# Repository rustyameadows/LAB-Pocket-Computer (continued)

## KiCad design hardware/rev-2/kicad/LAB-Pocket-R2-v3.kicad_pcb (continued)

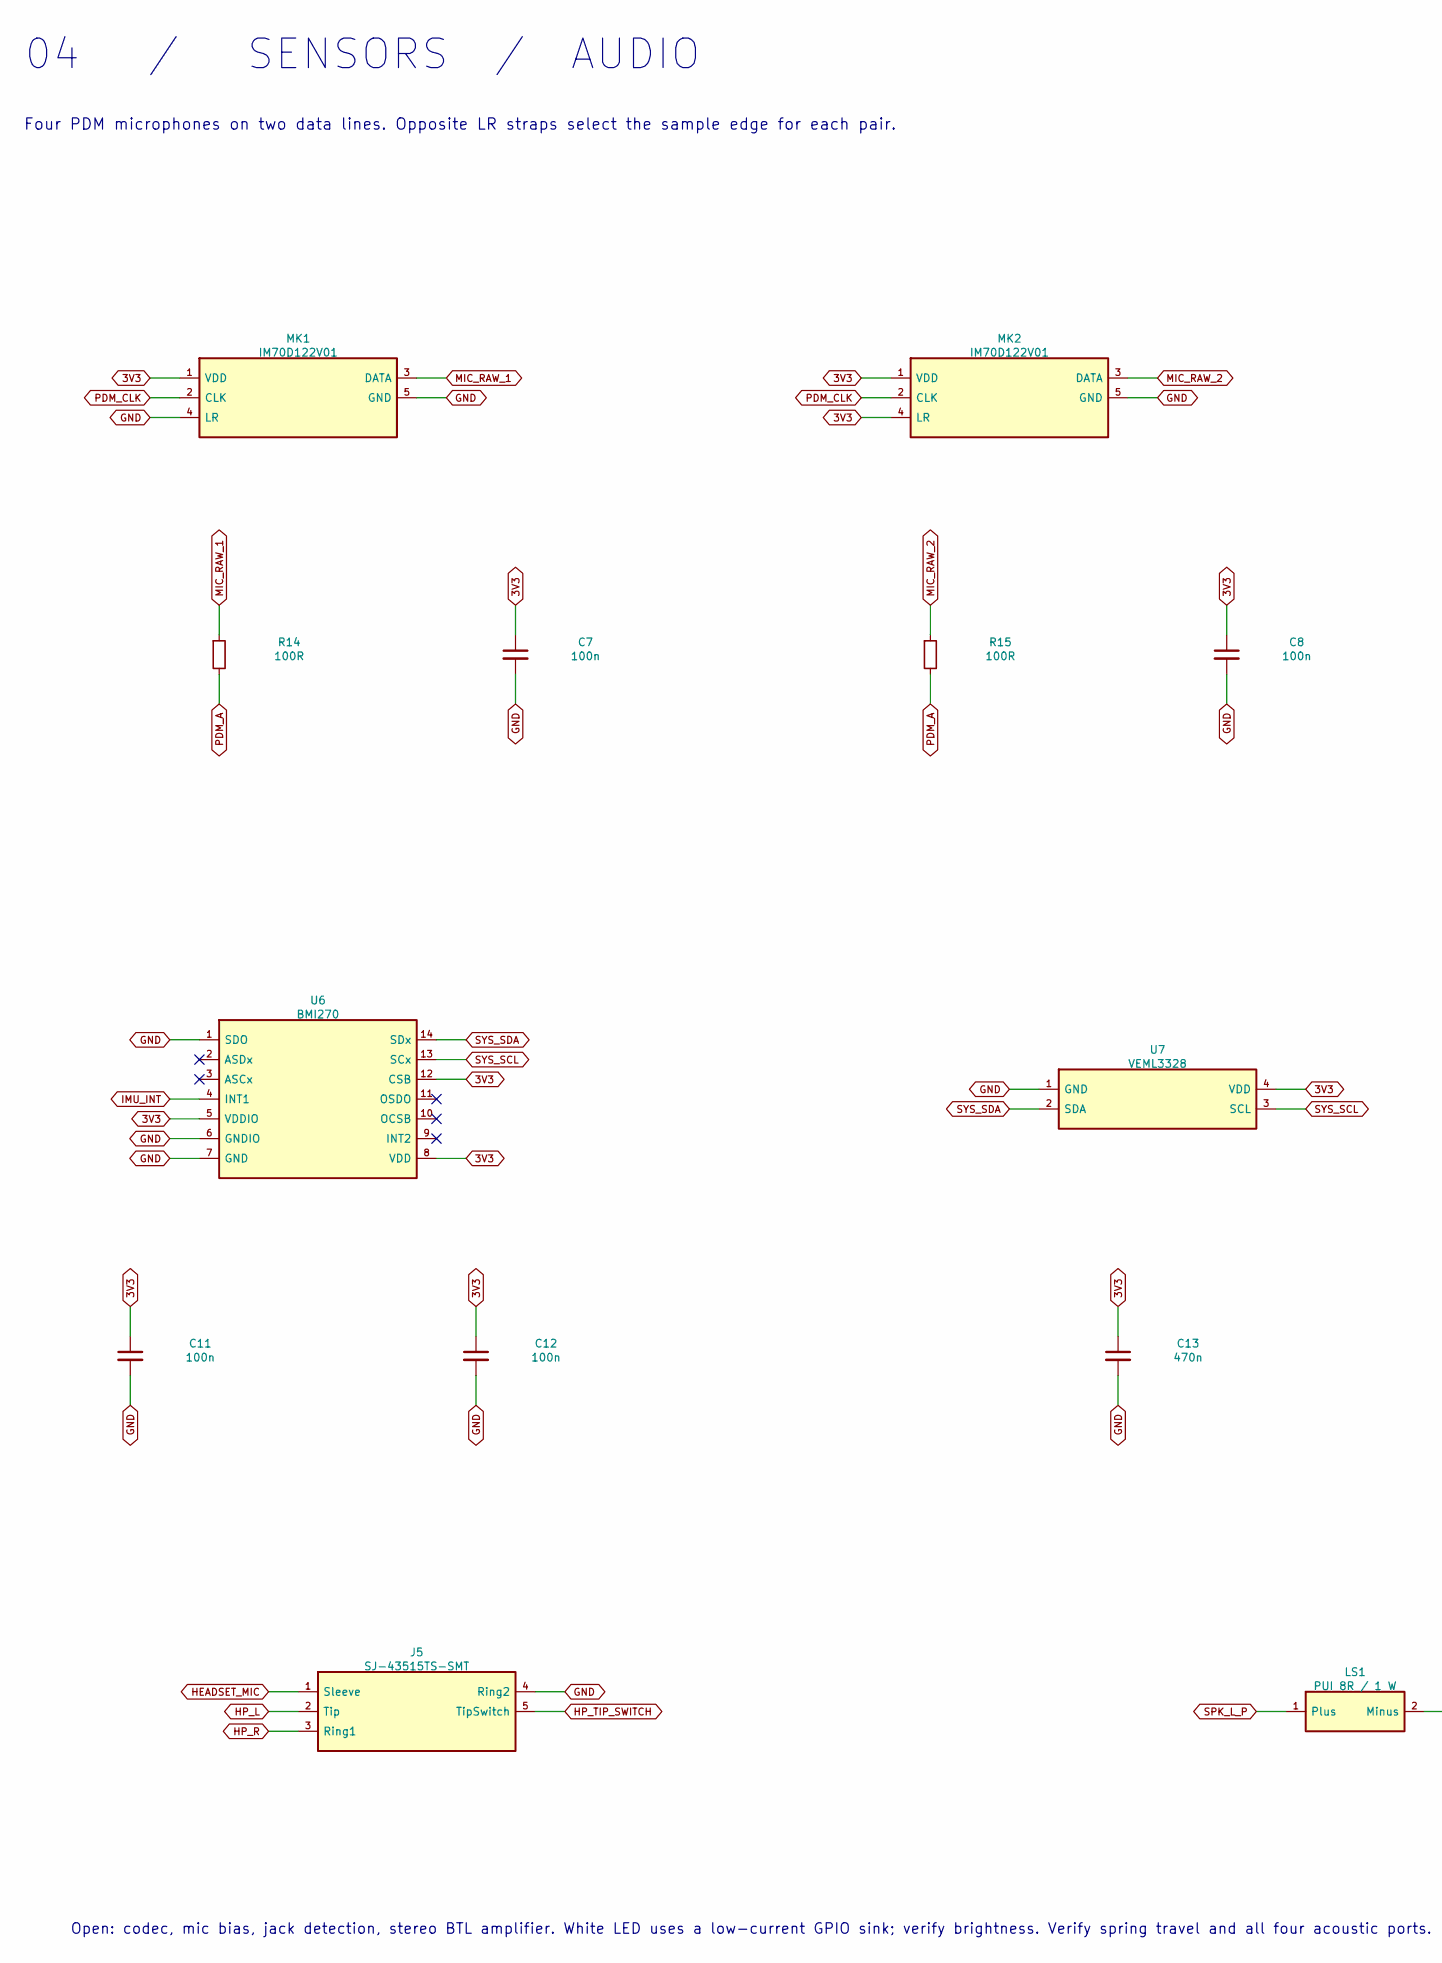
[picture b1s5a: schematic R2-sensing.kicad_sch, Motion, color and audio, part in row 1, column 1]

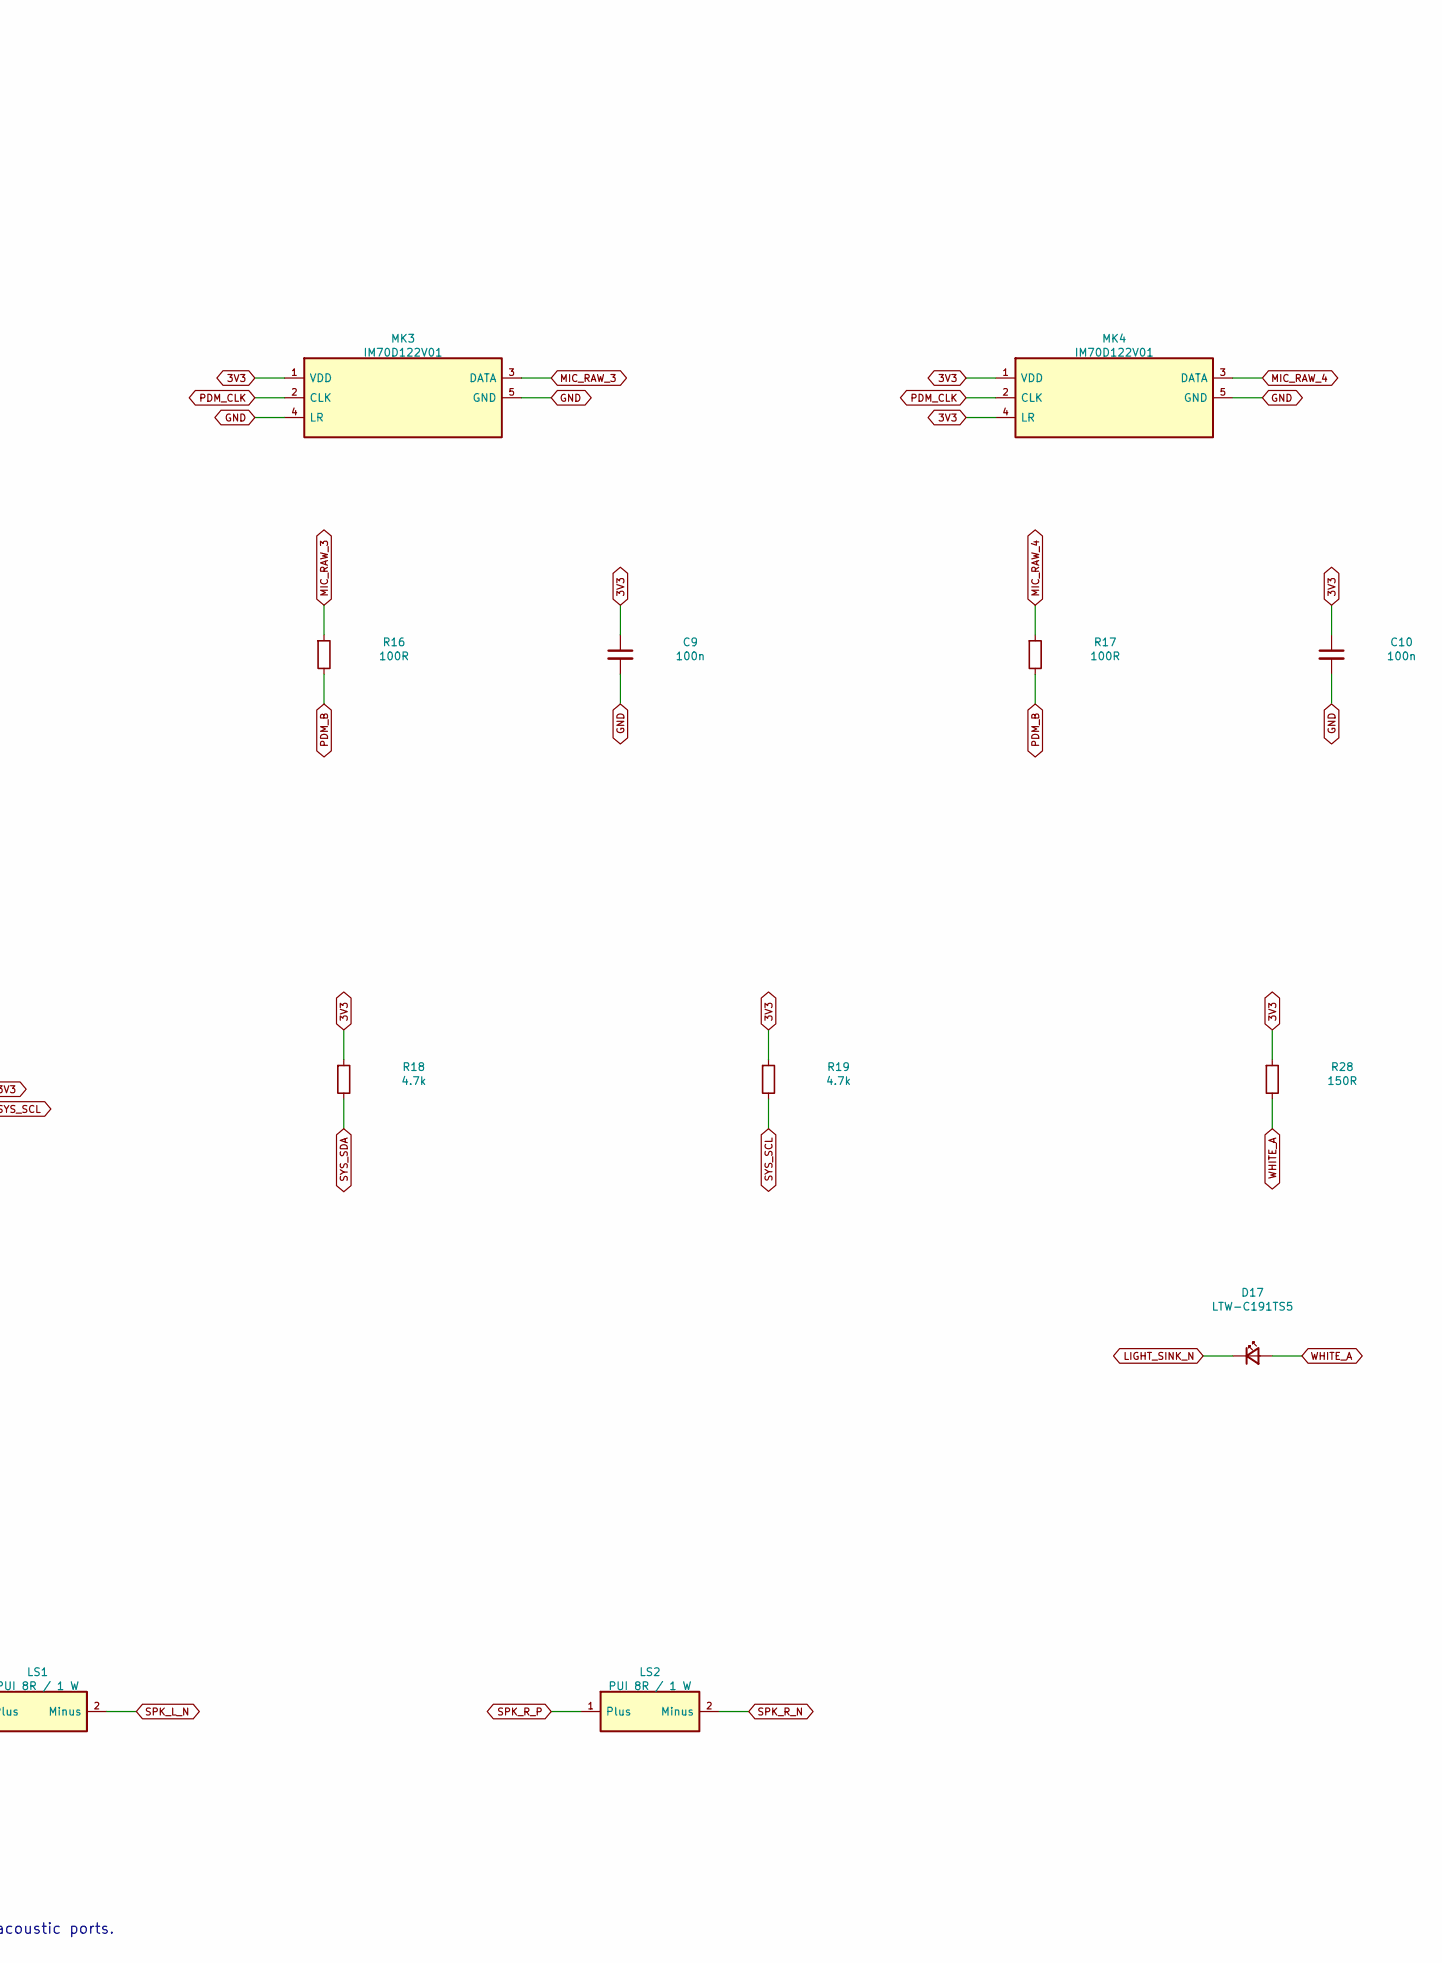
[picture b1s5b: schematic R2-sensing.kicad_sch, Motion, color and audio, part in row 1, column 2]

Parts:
C7, C8, C9, C10, C11, C12: 100n; C_0603_1608Metric; MPN C0603C104K5RACTU
C13: 470n; C_0603_1608Metric; MPN C0603C474K3RACTU
D17: LTW-C191TS5; LED_0603_1608Metric; MPN LTW-C191TS5
J5: SJ-43515TS-SMT; SJ-43515TS; MPN SJ-43515TS-SMT-TR
LS1, LS2: PUI 8R / 1 W; MPN AS01808AO-SC18-WP-R
MK1, MK2, MK3, MK4: IM70D122V01; IM70D122; MPN IM70D122V01XTMA1
R14, R15, R16, R17: 100R; R_0603_1608Metric; MPN CRCW0603100RFKEA
R18, R19: 4.7k; R_0603_1608Metric; MPN CRCW06034K70FKEA
R28: 150R; R_0603_1608Metric; MPN CRCW0603150RFKEA
U6: BMI270; Bosch_LGA-14_3x2.5mm_P0.5mm; MPN BMI270
U7: VEML3328; MPN VEML3328

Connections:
3V3: C7.1, C8.1, C9.1, C10.1, C11.1, C12.1, C13.1, MK1.1 (VDD), MK2.1 (VDD), MK2.4 (LR), MK3.1 (VDD), MK4.1 (VDD), MK4.4 (LR), R18.1, R19.1, R28.1, U6.5 (VDDIO), U6.8 (VDD), U6.12 (CSB), U7.4 (VDD); also elsewhere on the board
GND: C7.2, C8.2, C9.2, C10.2, C11.2, C12.2, C13.2, J5.4 (Ring2), MK1.4 (LR), MK1.5 (GND), MK2.5 (GND), MK3.4 (LR), MK3.5 (GND), MK4.5 (GND), U6.1 (SDO), U6.6 (GNDIO), U6.7 (GND), U7.1 (GND); also elsewhere on the board
HEADSET_MIC: J5.1 (Sleeve)
HP_L: J5.2 (Tip)
HP_R: J5.3 (Ring1)
HP_TIP_SWITCH: J5.5 (TipSwitch)
IMU_INT: U6.4 (INT1); also elsewhere on the board
LIGHT_SINK_N: D17.1 (K); also elsewhere on the board
MIC_RAW_1: MK1.3 (DATA), R14.1
MIC_RAW_2: MK2.3 (DATA), R15.1
MIC_RAW_3: MK3.3 (DATA), R16.1
MIC_RAW_4: MK4.3 (DATA), R17.1
PDM_A: R14.2, R15.2; also elsewhere on the board
PDM_B: R16.2, R17.2; also elsewhere on the board
PDM_CLK: MK1.2 (CLK), MK2.2 (CLK), MK3.2 (CLK), MK4.2 (CLK); also elsewhere on the board
SYS_SCL: R19.2, U6.13 (SCx), U7.3 (SCL); also elsewhere on the board
SYS_SDA: R18.2, U6.14 (SDx), U7.2 (SDA); also elsewhere on the board
WHITE_A: D17.2 (A), R28.2

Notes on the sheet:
04 / SENSORS / AUDIO
Four PDM microphones on two data lines. Opposite LR straps select the sample edge for each pair.
Open: codec, mic bias, jack detection, stereo BTL amplifier. White LED uses a low-current GPIO sink; verify brightness. Verify spring travel and all four acoustic ports.

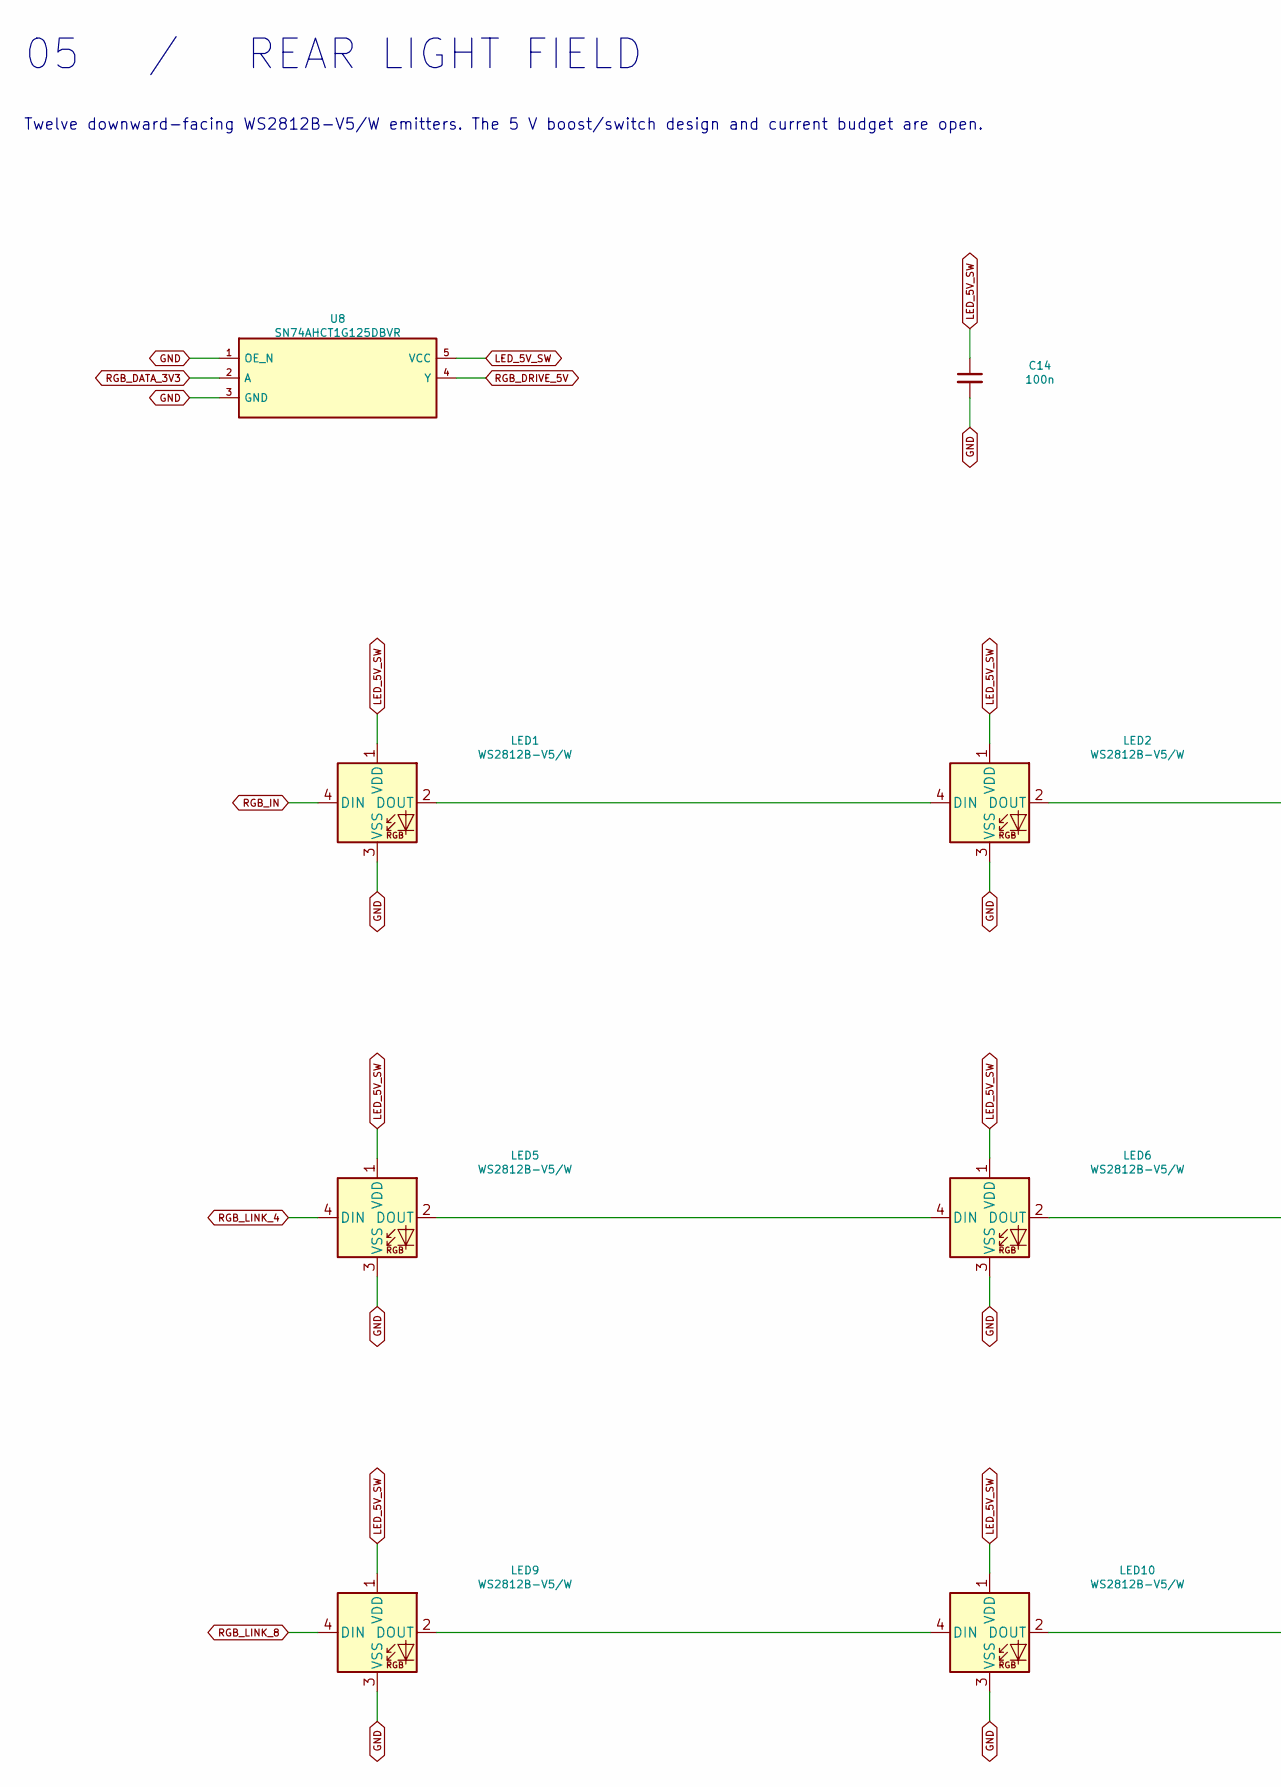
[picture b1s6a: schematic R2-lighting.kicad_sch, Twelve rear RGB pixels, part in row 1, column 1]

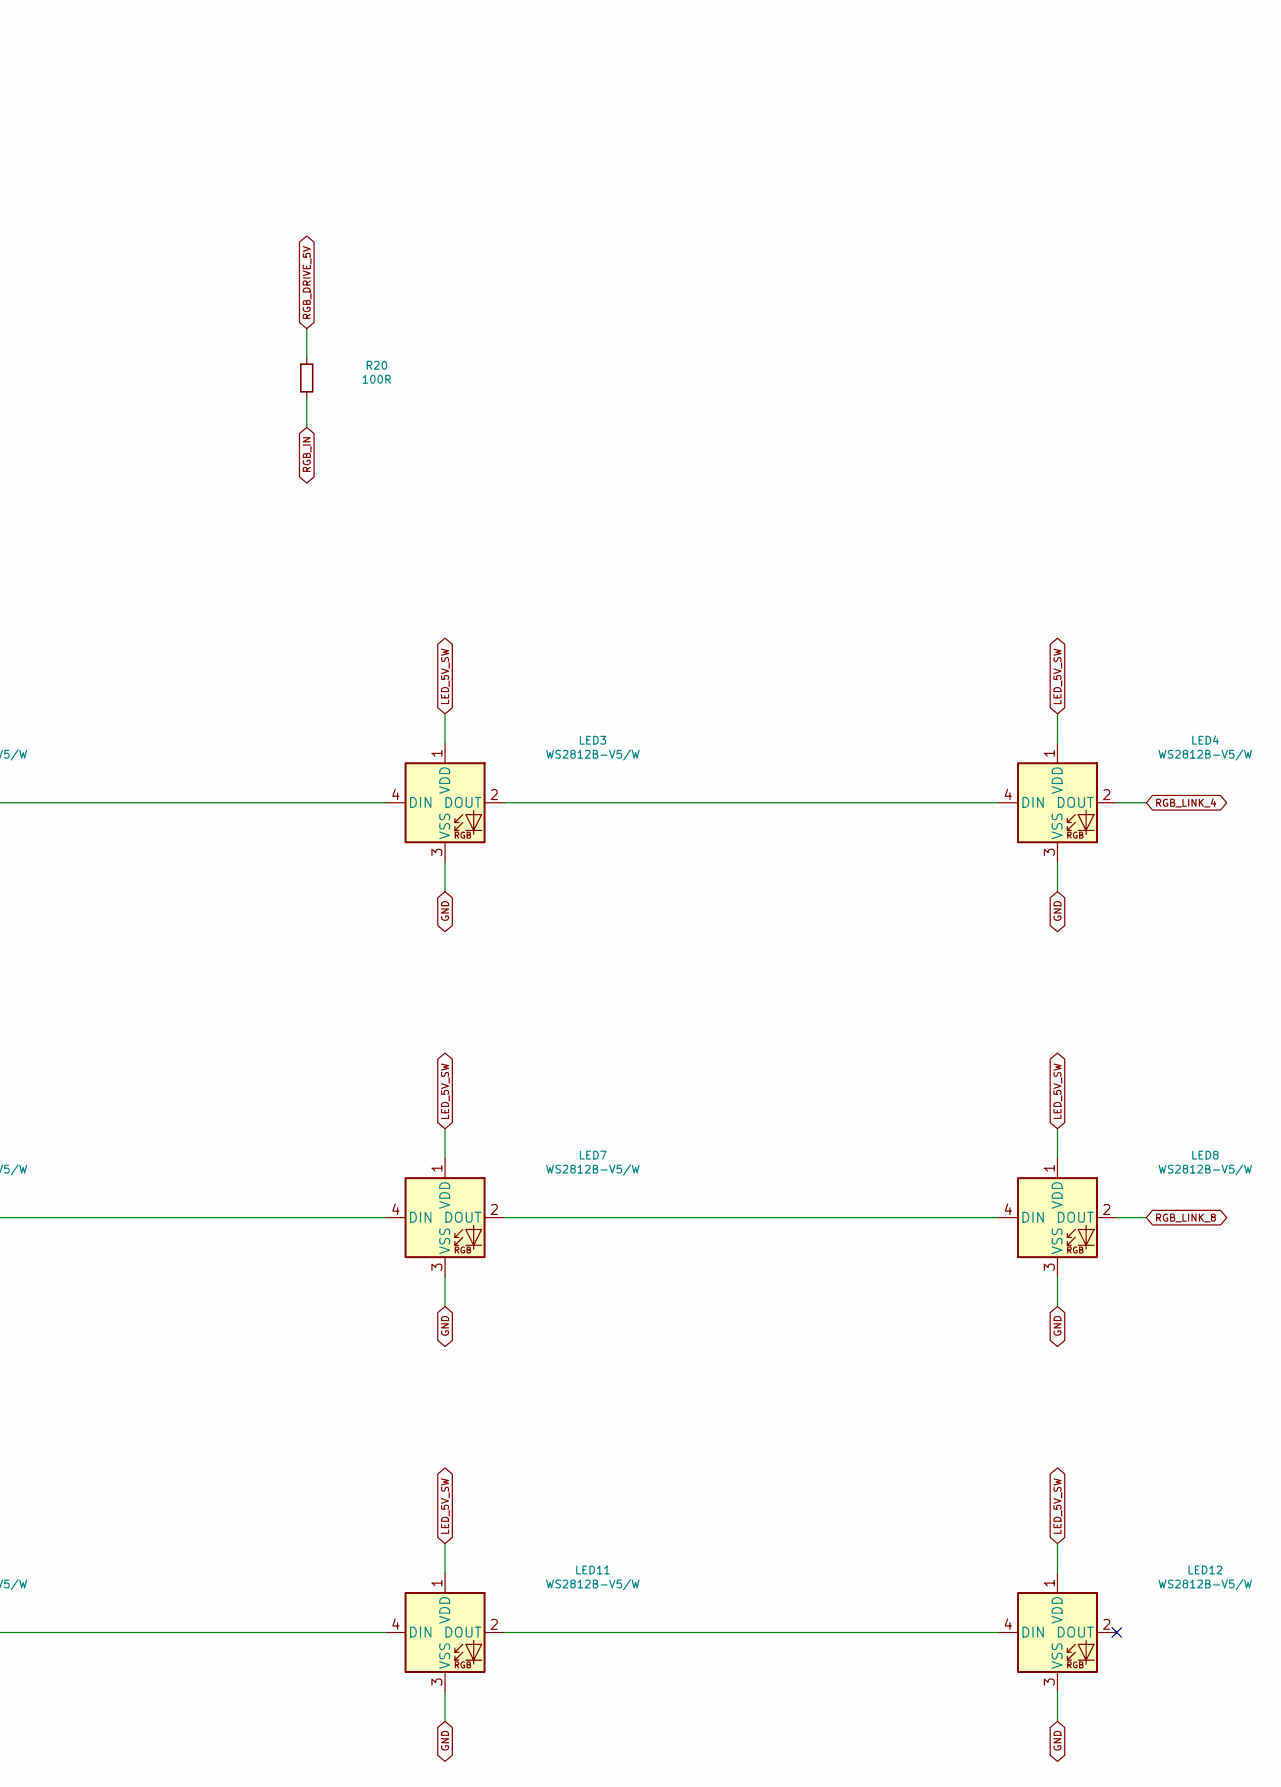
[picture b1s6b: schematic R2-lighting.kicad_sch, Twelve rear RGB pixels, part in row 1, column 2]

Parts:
C14: 100n; C_0603_1608Metric; MPN C0603C104K5RACTU
LED1, LED2, LED3, LED4, LED5, LED6, LED7, LED8, LED9, LED10, LED11, LED12: WS2812B-V5/W; LED_WS2812B_PLCC4_5.0x5.0mm_P3.2mm; MPN WS2812B-V5/W
R20: 100R; R_0603_1608Metric; MPN CRCW0603100RFKEA
U8: SN74AHCT1G125DBVR; SOT-23-5; MPN SN74AHCT1G125DBVR

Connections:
GND: C14.2, LED1.3 (VSS), LED2.3 (VSS), LED3.3 (VSS), LED4.3 (VSS), LED5.3 (VSS), LED6.3 (VSS), LED7.3 (VSS), LED8.3 (VSS), LED9.3 (VSS), LED10.3 (VSS), LED11.3 (VSS), LED12.3 (VSS), U8.1 (OE_N), U8.3 (GND); also elsewhere on the board
LED_5V_SW: C14.1, LED1.1 (VDD), LED2.1 (VDD), LED3.1 (VDD), LED4.1 (VDD), LED5.1 (VDD), LED6.1 (VDD), LED7.1 (VDD), LED8.1 (VDD), LED9.1 (VDD), LED10.1 (VDD), LED11.1 (VDD), LED12.1 (VDD), U8.5 (VCC)
unnamed: LED1.2 (DOUT), LED2.4 (DIN)
unnamed: LED2.2 (DOUT), LED3.4 (DIN)
unnamed: LED3.2 (DOUT), LED4.4 (DIN)
unnamed: LED5.2 (DOUT), LED6.4 (DIN)
unnamed: LED6.2 (DOUT), LED7.4 (DIN)
unnamed: LED7.2 (DOUT), LED8.4 (DIN)
unnamed: LED9.2 (DOUT), LED10.4 (DIN)
unnamed: LED10.2 (DOUT), LED11.4 (DIN)
unnamed: LED11.2 (DOUT), LED12.4 (DIN)
RGB_DATA_3V3: U8.2 (A); also elsewhere on the board
RGB_DRIVE_5V: R20.1, U8.4 (Y)
RGB_IN: LED1.4 (DIN), R20.2
RGB_LINK_4: LED4.2 (DOUT), LED5.4 (DIN)
RGB_LINK_8: LED8.2 (DOUT), LED9.4 (DIN)

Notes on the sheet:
05 / REAR LIGHT FIELD
Twelve downward-facing WS2812B-V5/W emitters. The 5 V boost/switch design and current budget are open.

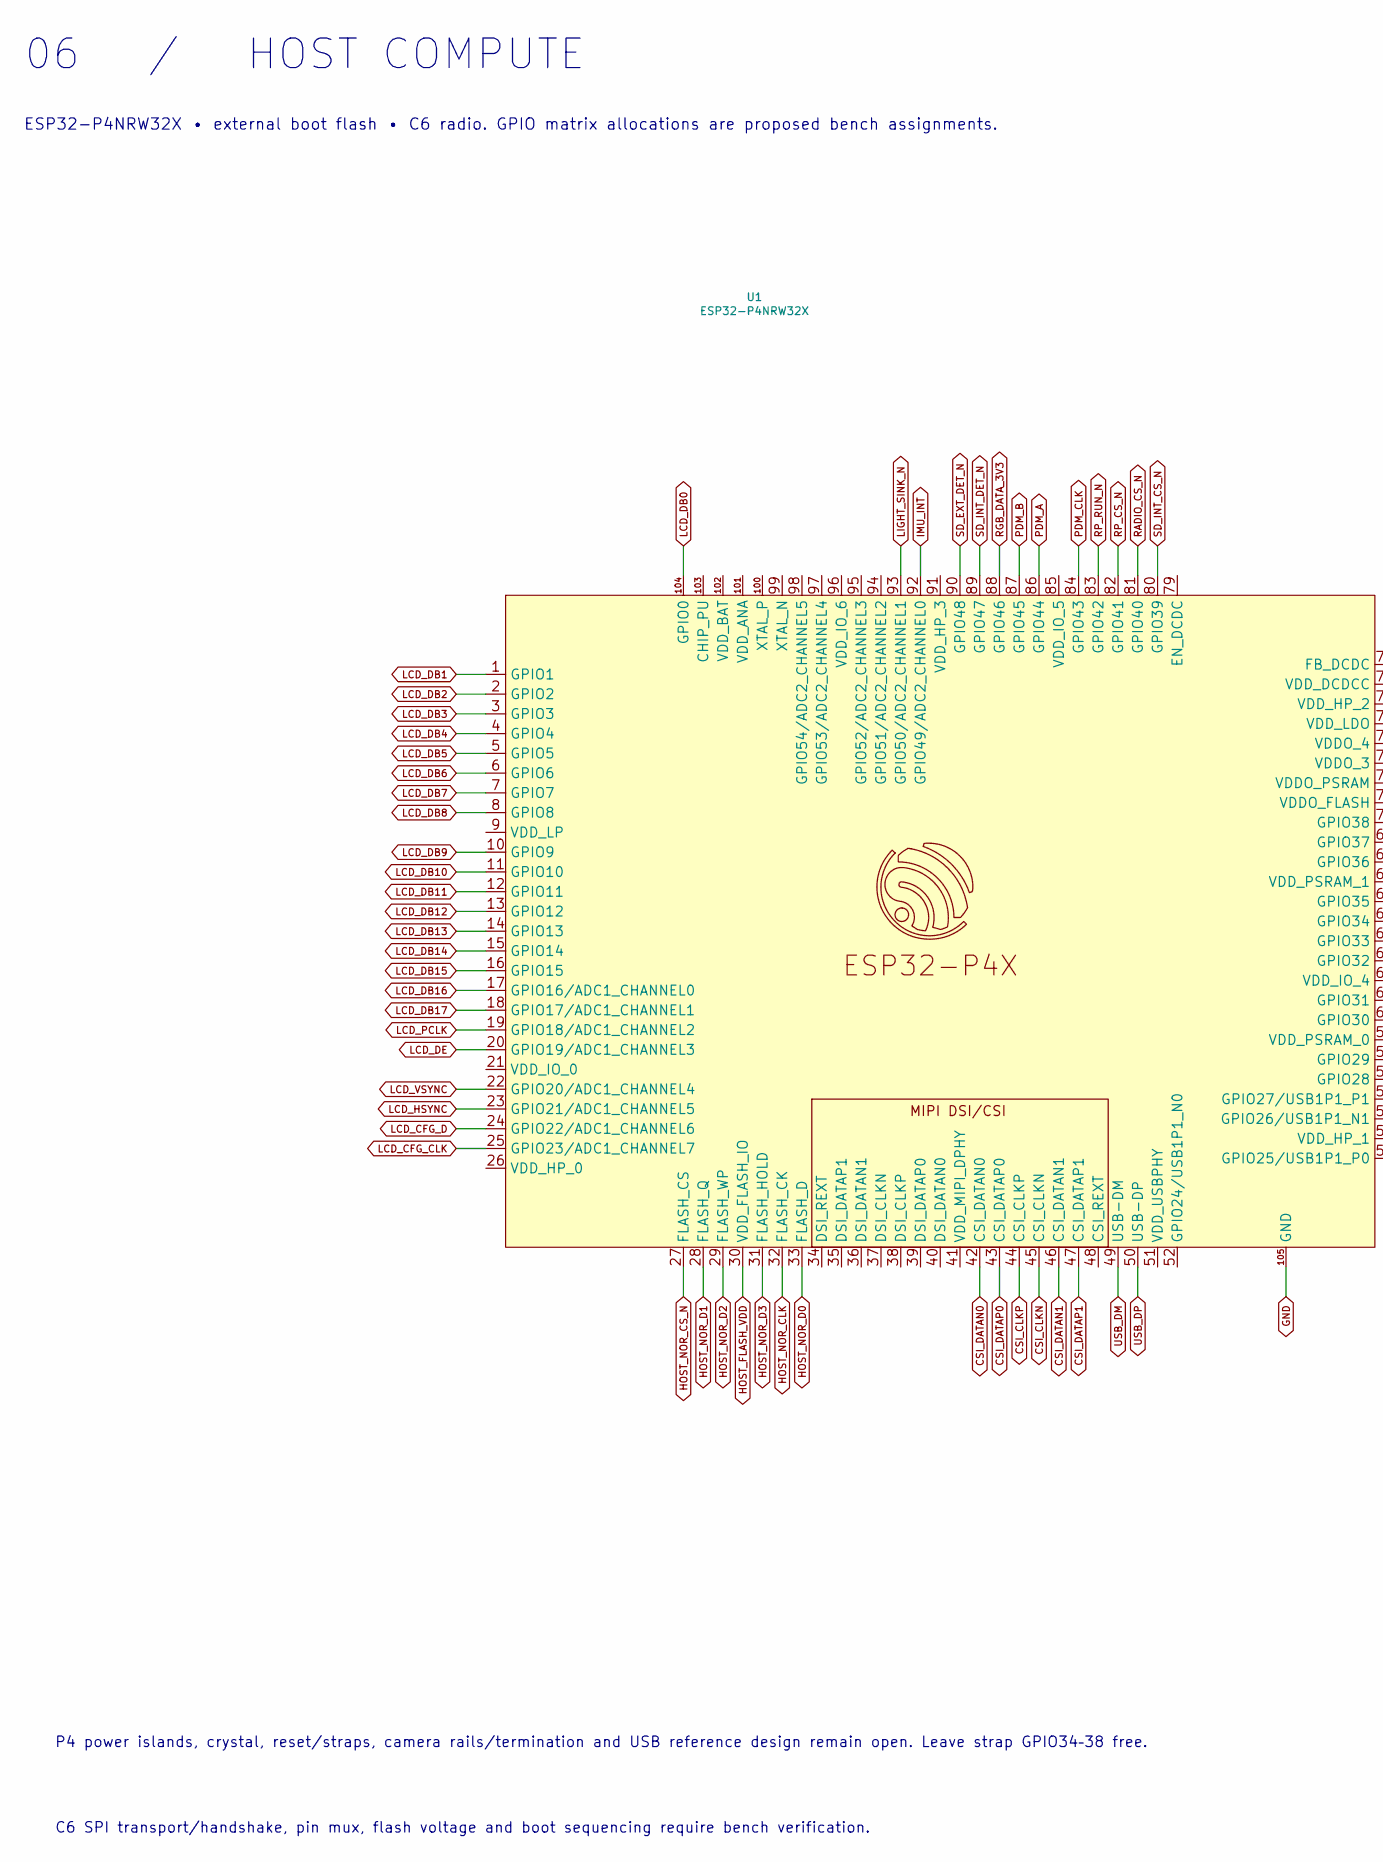
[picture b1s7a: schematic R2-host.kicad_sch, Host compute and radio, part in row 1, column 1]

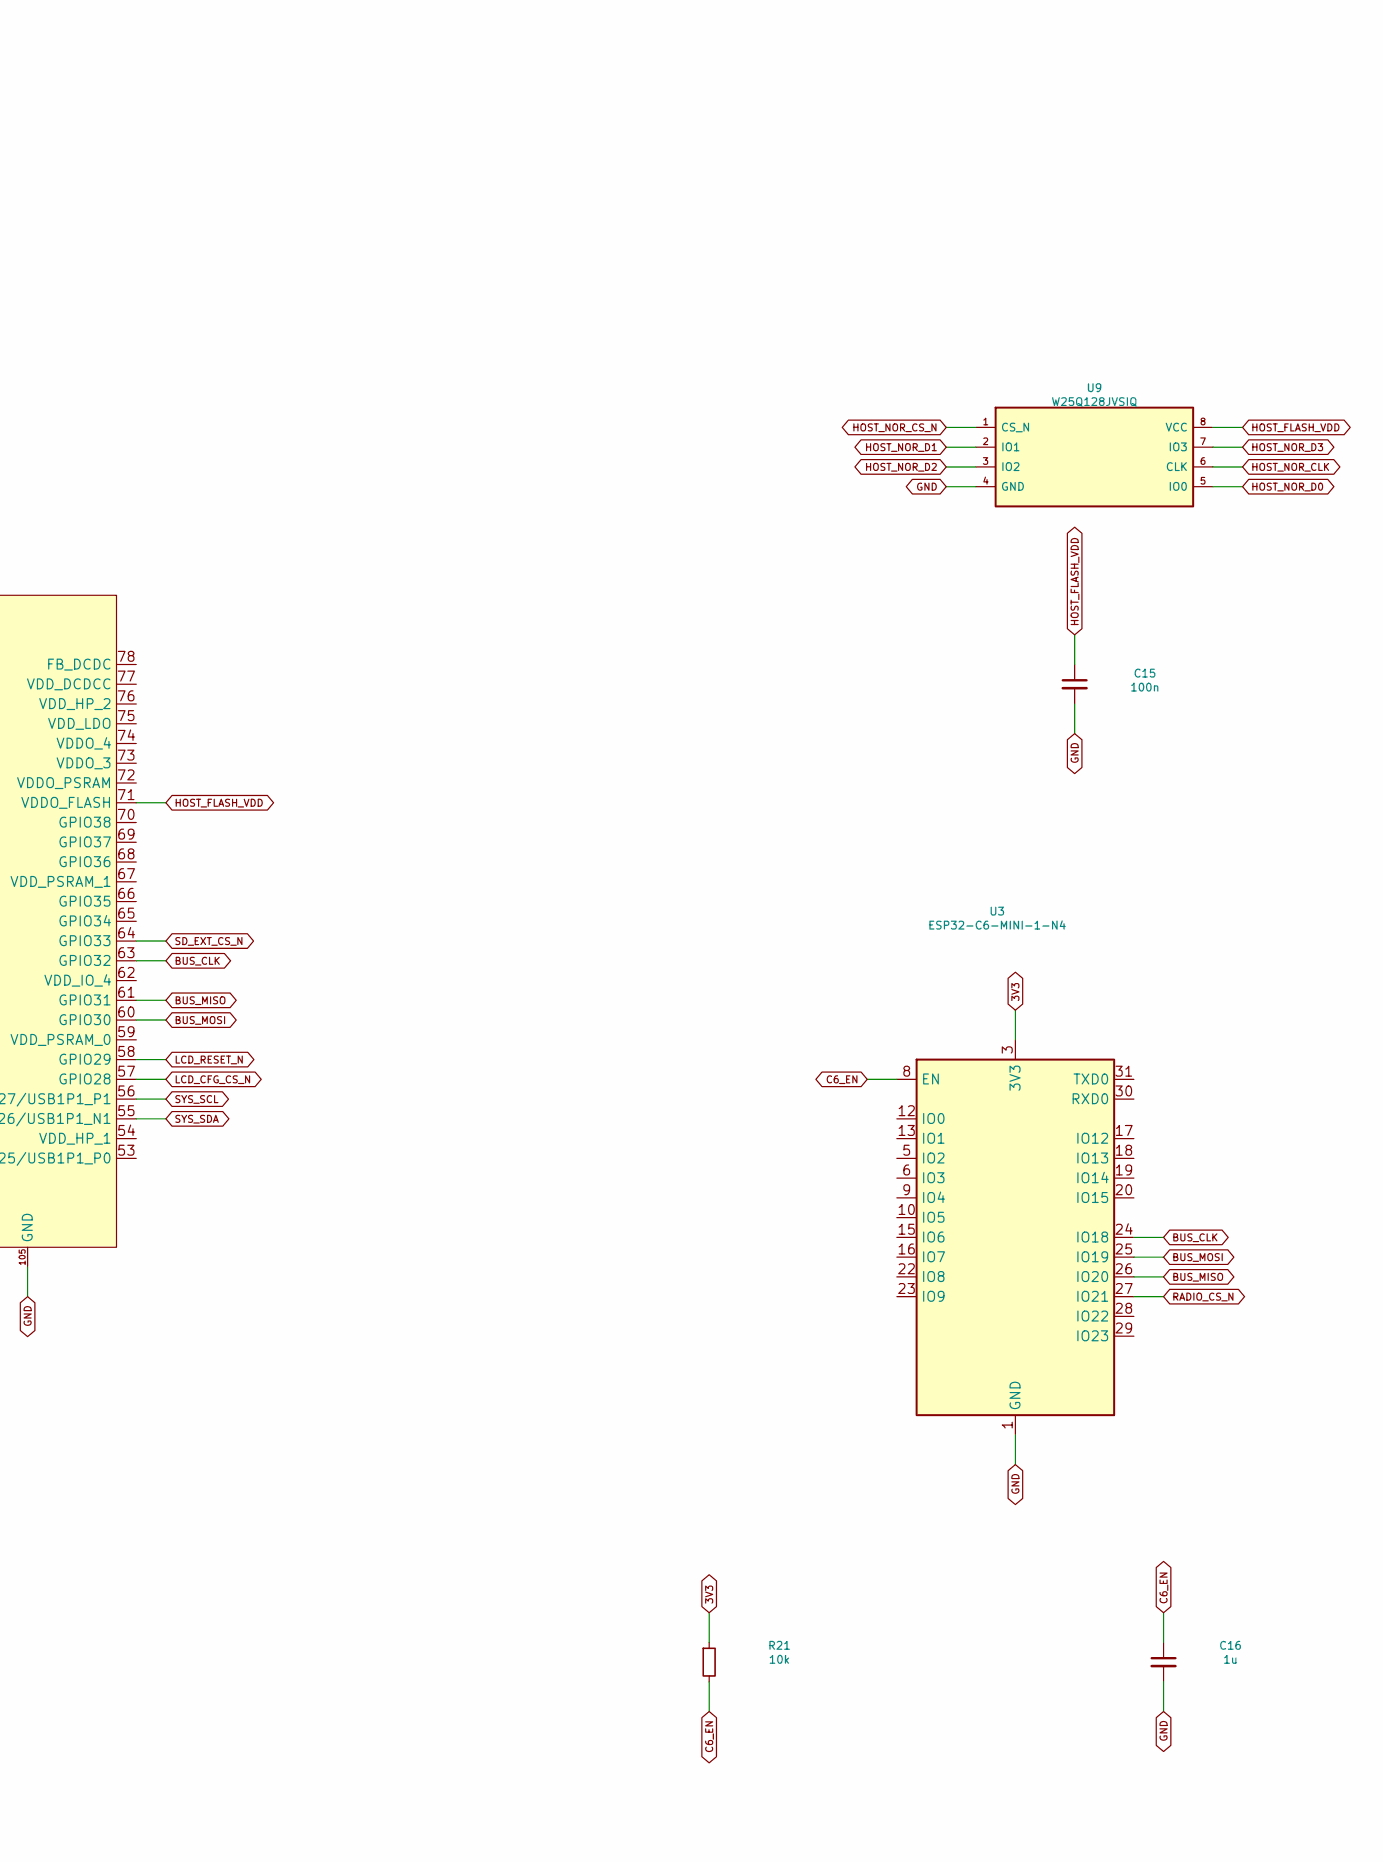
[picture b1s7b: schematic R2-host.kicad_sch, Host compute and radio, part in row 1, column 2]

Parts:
C15: 100n; C_0603_1608Metric; MPN C0603C104K5RACTU
C16: 1u; C_0603_1608Metric; MPN C0603C105K8PACTU
R21: 10k; R_0603_1608Metric; MPN CRCW060310K0FKEA
U1: ESP32-P4NRW32X; ESP32-P4; MPN ESP32-P4NRW32X
U3: ESP32-C6-MINI-1-N4; ESP32-C6-MINI-1; MPN ESP32-C6-MINI-1-N4
U9: W25Q128JVSIQ; SOIC-8_5.3x5.3mm_P1.27mm; MPN W25Q128JVSIQ

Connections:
3V3: R21.1, U3.3 (3V3); also elsewhere on the board
BUS_CLK: U1.63 (GPIO32), U3.24 (IO18); also elsewhere on the board
BUS_MISO: U1.61 (GPIO31), U3.26 (IO20); also elsewhere on the board
BUS_MOSI: U1.60 (GPIO30), U3.25 (IO19); also elsewhere on the board
C6_EN: C16.1, R21.2, U3.8 (EN)
CSI_CLKN: U1.45 (CSI_CLKN)
CSI_CLKP: U1.44 (CSI_CLKP)
CSI_DATAN0: U1.42 (CSI_DATAN0)
CSI_DATAN1: U1.46 (CSI_DATAN1)
CSI_DATAP0: U1.43 (CSI_DATAP0)
CSI_DATAP1: U1.47 (CSI_DATAP1)
GND: C15.2, C16.2, U1.105 (GND), U3.1 (GND), U3.2 (GND), U3.11 (GND), U3.14 (GND), U3.36 (GND), U3.37 (GND), U3.38 (GND), U3.39 (GND), U3.40 (GND), U3.41 (GND), U3.42 (GND), U3.43 (GND), U3.44 (GND), U3.45 (GND), U3.46 (GND), U3.47 (GND), U3.48 (GND), U3.49 (GND), U3.50 (GND), U3.51 (GND), U3.52 (GND), U3.53 (GND), U9.4 (GND); also elsewhere on the board
HOST_FLASH_VDD: C15.1, U1.30 (VDD_FLASH_IO), U1.71 (VDDO_FLASH), U9.8 (VCC)
HOST_NOR_CLK: U1.32 (FLASH_CK), U9.6 (CLK)
HOST_NOR_CS_N: U1.27 (FLASH_CS), U9.1 (CS_N)
HOST_NOR_D0: U1.33 (FLASH_D), U9.5 (IO0)
HOST_NOR_D1: U1.28 (FLASH_Q), U9.2 (IO1)
HOST_NOR_D2: U1.29 (FLASH_WP), U9.3 (IO2)
HOST_NOR_D3: U1.31 (FLASH_HOLD), U9.7 (IO3)
IMU_INT: U1.92 (GPIO49/ADC2_CHANNEL0); also elsewhere on the board
LCD_CFG_CLK: U1.25 (GPIO23/ADC1_CHANNEL7); also elsewhere on the board
LCD_CFG_CS_N: U1.57 (GPIO28); also elsewhere on the board
LCD_CFG_D: U1.24 (GPIO22/ADC1_CHANNEL6); also elsewhere on the board
LCD_DB0: U1.104 (GPIO0); also elsewhere on the board
LCD_DB1: U1.1 (GPIO1); also elsewhere on the board
LCD_DB2: U1.2 (GPIO2); also elsewhere on the board
LCD_DB3: U1.3 (GPIO3); also elsewhere on the board
LCD_DB4: U1.4 (GPIO4); also elsewhere on the board
LCD_DB5: U1.5 (GPIO5); also elsewhere on the board
LCD_DB6: U1.6 (GPIO6); also elsewhere on the board
LCD_DB7: U1.7 (GPIO7); also elsewhere on the board
LCD_DB8: U1.8 (GPIO8); also elsewhere on the board
LCD_DB9: U1.10 (GPIO9); also elsewhere on the board
LCD_DB10: U1.11 (GPIO10); also elsewhere on the board
LCD_DB11: U1.12 (GPIO11); also elsewhere on the board
LCD_DB12: U1.13 (GPIO12); also elsewhere on the board
LCD_DB13: U1.14 (GPIO13); also elsewhere on the board
LCD_DB14: U1.15 (GPIO14); also elsewhere on the board
LCD_DB15: U1.16 (GPIO15); also elsewhere on the board
LCD_DB16: U1.17 (GPIO16/ADC1_CHANNEL0); also elsewhere on the board
LCD_DB17: U1.18 (GPIO17/ADC1_CHANNEL1); also elsewhere on the board
LCD_DE: U1.20 (GPIO19/ADC1_CHANNEL3); also elsewhere on the board
LCD_HSYNC: U1.23 (GPIO21/ADC1_CHANNEL5); also elsewhere on the board
LCD_PCLK: U1.19 (GPIO18/ADC1_CHANNEL2); also elsewhere on the board
LCD_RESET_N: U1.58 (GPIO29); also elsewhere on the board
LCD_VSYNC: U1.22 (GPIO20/ADC1_CHANNEL4); also elsewhere on the board
LIGHT_SINK_N: U1.93 (GPIO50/ADC2_CHANNEL1); also elsewhere on the board
PDM_A: U1.86 (GPIO44); also elsewhere on the board
PDM_B: U1.87 (GPIO45); also elsewhere on the board
PDM_CLK: U1.84 (GPIO43); also elsewhere on the board
RADIO_CS_N: U1.81 (GPIO40), U3.27 (IO21)
RGB_DATA_3V3: U1.88 (GPIO46); also elsewhere on the board
RP_CS_N: U1.82 (GPIO41); also elsewhere on the board
RP_RUN_N: U1.83 (GPIO42); also elsewhere on the board
SD_EXT_CS_N: U1.64 (GPIO33); also elsewhere on the board
SD_EXT_DET_N: U1.90 (GPIO48); also elsewhere on the board
SD_INT_CS_N: U1.80 (GPIO39); also elsewhere on the board
SD_INT_DET_N: U1.89 (GPIO47); also elsewhere on the board
SYS_SCL: U1.56 (GPIO27/USB1P1_P1); also elsewhere on the board
SYS_SDA: U1.55 (GPIO26/USB1P1_N1); also elsewhere on the board
USB_DM: U1.49 (USB-DM); also elsewhere on the board
USB_DP: U1.50 (USB-DP); also elsewhere on the board

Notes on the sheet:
06 / HOST COMPUTE
ESP32-P4NRW32X • external boot flash • C6 radio. GPIO matrix allocations are proposed bench assignments.
P4 power islands, crystal, reset/straps, camera rails/termination and USB reference design remain open. Leave strap GPIO34–38 free.
C6 SPI transport/handshake, pin mux, flash voltage and boot sequencing require bench verification.
